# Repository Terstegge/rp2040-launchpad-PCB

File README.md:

# RP2040-Launchpad PCB

This repository contains the KiCad design files for a TI-style Launchpad board
with the RP2040 microcontroller. The board features a build-in picoprobe
debugger, which signals UART RX/TX and SWD activity with 3 LEDs. The unused
GPIO pins of the picoprobe are connected to a header, which could be used
in the future for more functionality like a simple logic analyzer etc.

The target RP2040 controller has 2 connected pushbuttons, one normal LED and
8 WS2812-2020 LEDs as input/output. Some signals are also available on a
horizonal header at the lower end of the PCB, which is used to connect WLAN or
Bluetooth boards like WifiTick. Both RP2040 (target and picoprobe) use a
4 MiB flash chip. The target RP2040 also has a button to enable programming
via the target USB port (mass storage device). Normally this button is
not needed, because all programming and debugging of the target is performed
via the picoprobe using openocd and gdb.

The board also contains a LiPo-charger to enable battery-powered projects.

Why was this board designed? I have been using the MSP432 Launchpad from TI for
quite a while in university classes teaching microcontroller technology.
Unfortunately TI has stopped producing all MSP432-related products. Still we
have purchased lots of TI boosterpack-boards like the Educational Boosterpack MK II.
The be able to used these Boosterpacks also in the future, a new Launchpad had
to be found. The RP2040 is a very interesting microcontroller, and, what is
quite important for educational purposes, it has excellent documentation.
So some days were spent and this board came to life.

The pictures below show version 1.1, which only had 2 WS2812 LEDS, which were
quite big and bright. The current version 1.2 contains 8 smaller WS2812-2020
LEDs. The pictures will be updated as soon as prototypes for the new version
are available.

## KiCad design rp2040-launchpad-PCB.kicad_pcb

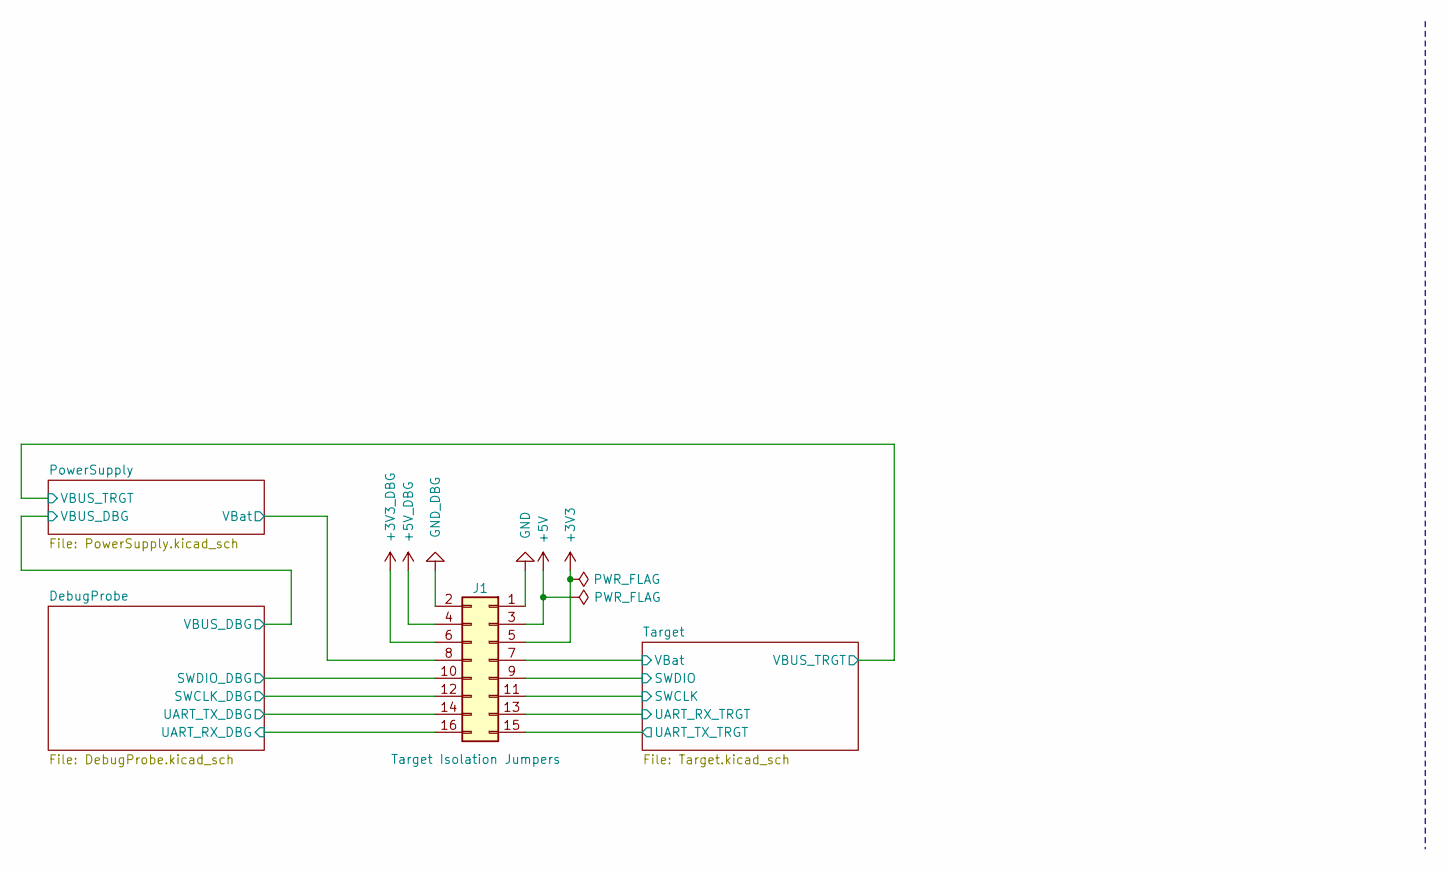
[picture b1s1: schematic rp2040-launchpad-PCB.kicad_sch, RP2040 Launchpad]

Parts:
J1: Target Isolation Jumpers; PinHeader_2x08_P2.54mm_Vertical

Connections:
+3V3: J1.5; also elsewhere on the board
+3V3_DBG: J1.6; also elsewhere on the board
+5V: J1.3; also elsewhere on the board
+5V_DBG: J1.4; also elsewhere on the board
/DebugProbe/SWCLK_DBG: J1.12; also elsewhere on the board
/DebugProbe/SWDIO_DBG: J1.10; also elsewhere on the board
/DebugProbe/UART_RX_DBG: J1.16; also elsewhere on the board
/DebugProbe/UART_TX_DBG: J1.14; also elsewhere on the board
/PowerSupply/VBat: J1.8; also elsewhere on the board
/Target/SWCLK: J1.11; also elsewhere on the board
/Target/SWDIO: J1.9; also elsewhere on the board
/Target/UART_RX_TRGT: J1.13; also elsewhere on the board
/Target/UART_TX_TRGT: J1.15; also elsewhere on the board
/Target/VBat: J1.7; also elsewhere on the board
GND: J1.1; also elsewhere on the board
GND_DBG: J1.2; also elsewhere on the board

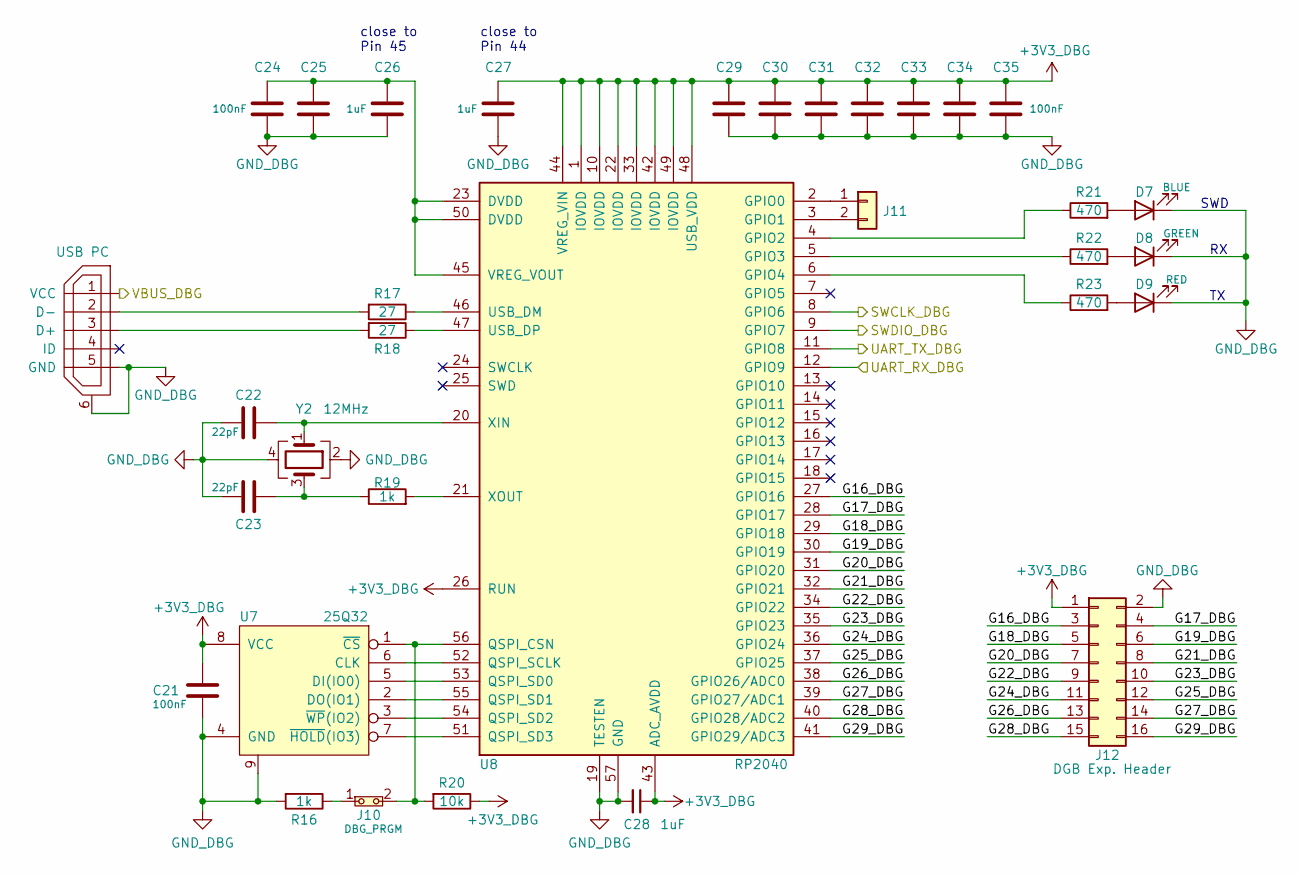
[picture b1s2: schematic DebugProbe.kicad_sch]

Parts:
C21, C24, C25, C29, C30, C31, C32, C33, C34, C35: 100nF; C_0603_1608Metric
C22, C23: 22pF; C_0603_1608Metric
C26, C27, C28: 1uF; C_0603_1608Metric
D7: BLUE; LED_0603_1608Metric
D8: GREEN; LED_0603_1608Metric
D9: RED; LED_0603_1608Metric
J10: DBG_PRGM; PinHeader_1x02_P2.54mm_Vertical
J11: UART_DBG; PinHeader_1x02_P2.54mm_Vertical
J12: DGB Exp. Header; PinHeader_2x08_P2.54mm_Vertical
R16, R19: 1k; R_0603_1608Metric
R17, R18: 27; R_0603_1608Metric
R20: 10k; R_0603_1608Metric
R21, R22, R23: 470; R_0603_1608Metric
U7: 25Q32; WSON-8-1EP_6x5mm_P1.27mm_EP3.4x4.3mm
U8: RP2040; QFN40P700X700X90-57N; PARTREV 1.6.1
USB2: USB PC; USB-micro-B-Amph-10118194
Y2: 12MHz; Crystal_SMD_TXC_7M-4Pin_3.2x2.5mm

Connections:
+3V3_DBG: C21.1, C27.1, C28.1, C29.1, C30.1, C31.1, C32.1, C33.1, C34.1, C35.1, J12.1, R20.1, U7.8 (VCC), U8.1 (IOVDD), U8.10 (IOVDD), U8.22 (IOVDD), U8.26 (RUN), U8.33 (IOVDD), U8.42 (IOVDD), U8.43 (ADC_AVDD), U8.44 (VREG_VIN), U8.48 (USB_VDD), U8.49 (IOVDD); also elsewhere on the board
/DebugProbe/G16_DBG: J12.3, U8.27 (GPIO16)
/DebugProbe/G17_DBG: J12.4, U8.28 (GPIO17)
/DebugProbe/G18_DBG: J12.5, U8.29 (GPIO18)
/DebugProbe/G19_DBG: J12.6, U8.30 (GPIO19)
/DebugProbe/G20_DBG: J12.7, U8.31 (GPIO20)
/DebugProbe/G21_DBG: J12.8, U8.32 (GPIO21)
/DebugProbe/G22_DBG: J12.9, U8.34 (GPIO22)
/DebugProbe/G23_DBG: J12.10, U8.35 (GPIO23)
/DebugProbe/G24_DBG: J12.11, U8.36 (GPIO24)
/DebugProbe/G25_DBG: J12.12, U8.37 (GPIO25)
/DebugProbe/G26_DBG: J12.13, U8.38 (GPIO26/ADC0)
/DebugProbe/G27_DBG: J12.14, U8.39 (GPIO27/ADC1)
/DebugProbe/G28_DBG: J12.15, U8.40 (GPIO28/ADC2)
/DebugProbe/G29_DBG: J12.16, U8.41 (GPIO29/ADC3)
/DebugProbe/SWCLK_DBG: U8.8 (GPIO6); also elsewhere on the board
/DebugProbe/SWDIO_DBG: U8.9 (GPIO7); also elsewhere on the board
/DebugProbe/UART_RX_DBG: U8.12 (GPIO9); also elsewhere on the board
/DebugProbe/UART_TX_DBG: U8.11 (GPIO8); also elsewhere on the board
/DebugProbe/VBUS_DBG: USB2.1 (VCC); also elsewhere on the board
GND_DBG: C21.2, C22.1, C23.1, C24.2, C25.2, C26.2, C27.2, C28.2, C29.2, C30.2, C31.2, C32.2, C33.2, C34.2, C35.2, D7.1 (K), D8.1 (K), D9.1 (K), J12.2, R16.2, U7.4 (GND), U7.9, U8.19 (TESTEN), U8.57 (GND), USB2.5 (GND), USB2.6, Y2.2, Y2.4; also elsewhere on the board
unnamed: C22.2, U8.20 (XIN), Y2.1
unnamed: C23.2, R19.1, Y2.3
unnamed: C24.1, C25.1, C26.1, U8.23 (DVDD), U8.45 (VREG_VOUT), U8.50 (DVDD)
unnamed: D7.2 (A), R21.2
unnamed: D8.2 (A), R22.2
unnamed: D9.2 (A), R23.2
unnamed: J10.1, R16.1
unnamed: J10.2, R20.2, U7.1 (~CS), U8.56 (QSPI_CSN)
unnamed: J11.1, U8.2 (GPIO0)
unnamed: J11.2, U8.3 (GPIO1)
unnamed: R17.1, U8.46 (USB_DM)
unnamed: R17.2, USB2.2 (D-)
unnamed: R18.1, U8.47 (USB_DP)
unnamed: R18.2, USB2.3 (D+)
unnamed: R19.2, U8.21 (XOUT)
unnamed: R21.1, U8.4 (GPIO2)
unnamed: R22.1, U8.5 (GPIO3)
unnamed: R23.1, U8.6 (GPIO4)
unnamed: U7.2 (DO(IO1)), U8.55 (QSPI_SD1)
unnamed: U7.3 (~WP(IO2)), U8.54 (QSPI_SD2)
unnamed: U7.5 (DI(IO0)), U8.53 (QSPI_SD0)
unnamed: U7.6 (CLK), U8.52 (QSPI_SCLK)
unnamed: U7.7 (~HOLD(IO3)), U8.51 (QSPI_SD3)

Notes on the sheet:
SWD
close to Pin 45
close to Pin 44

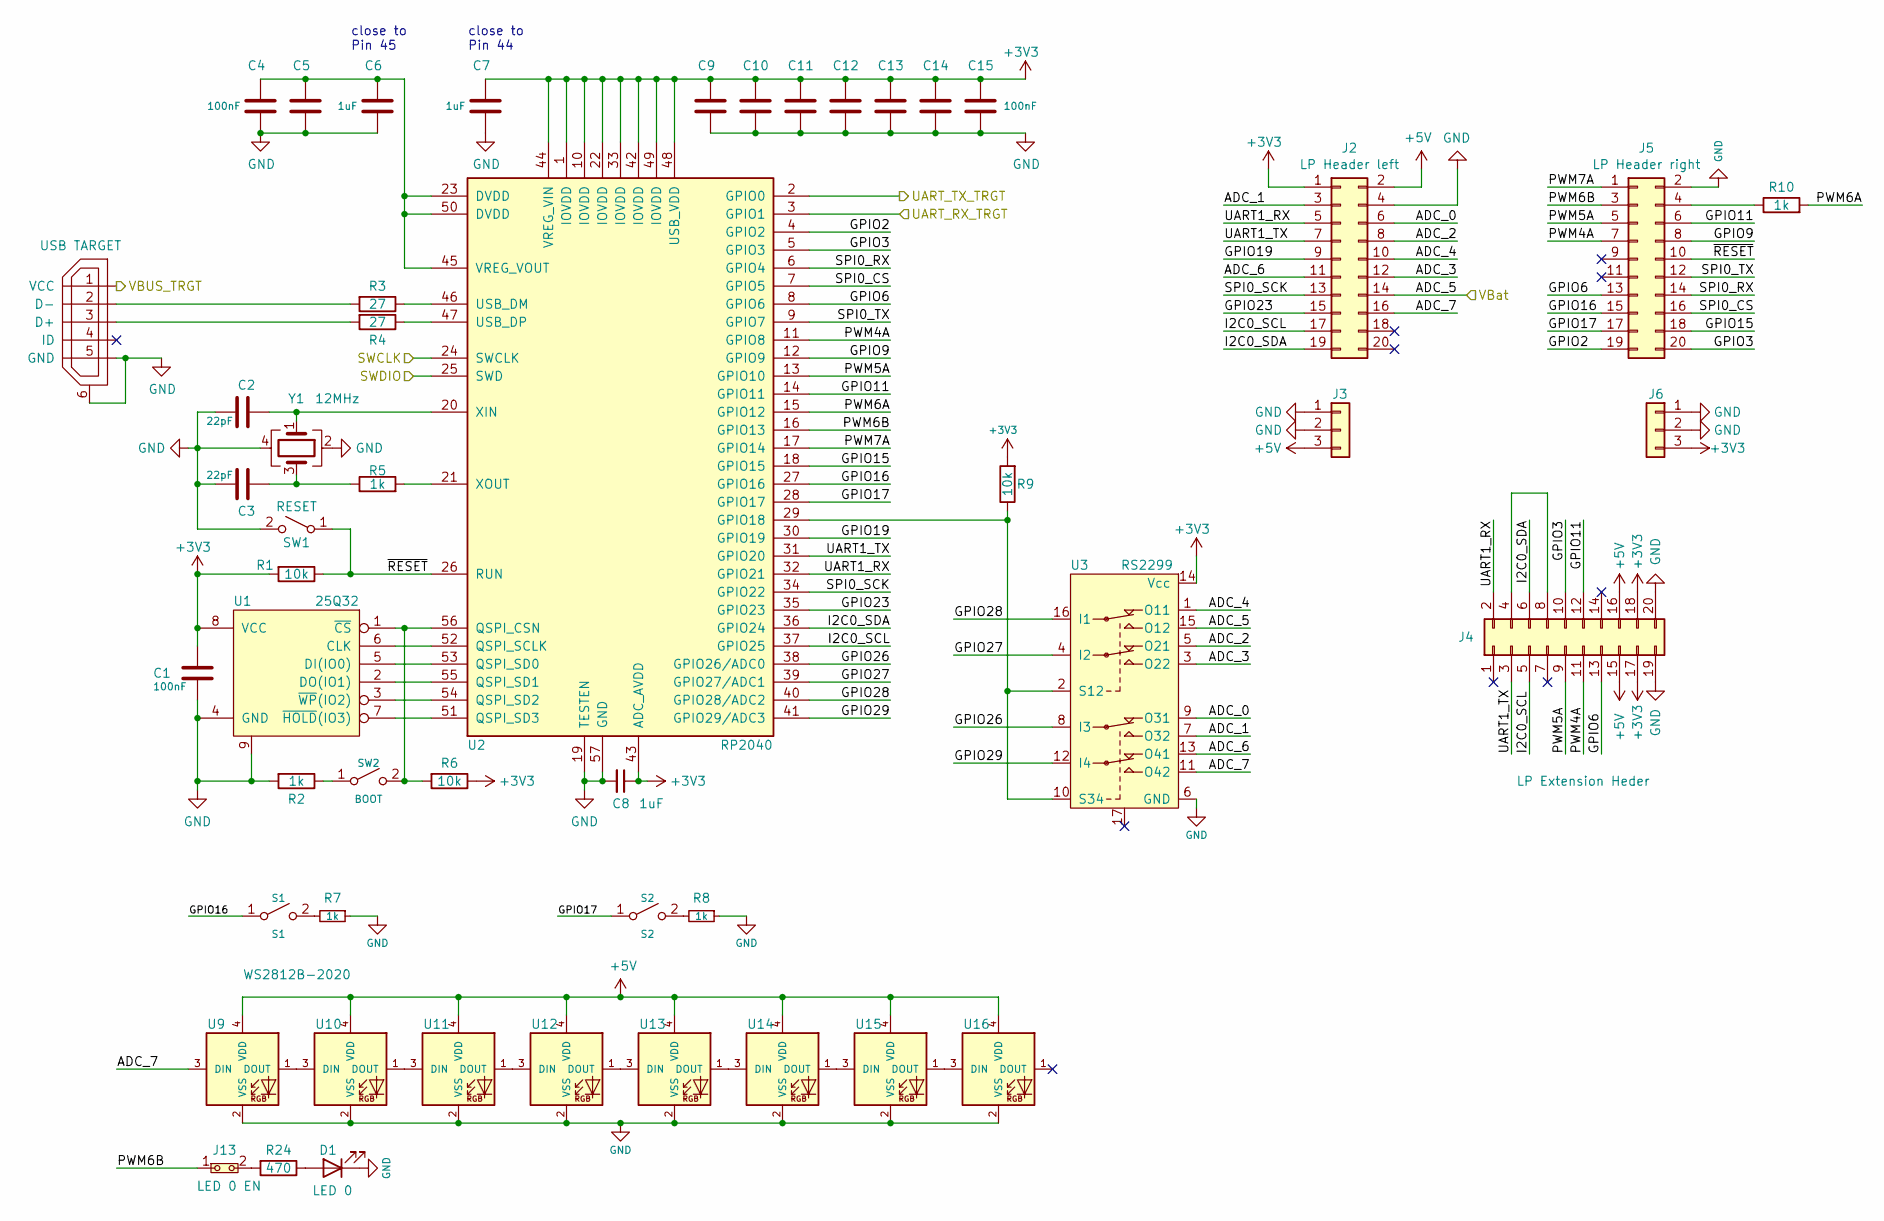
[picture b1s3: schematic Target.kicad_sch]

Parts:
C1, C4, C5, C9, C10, C11, C12, C13, C14, C15: 100nF; C_0603_1608Metric
C2, C3: 22pF; C_0603_1608Metric
C6, C7, C8: 1uF; C_0603_1608Metric
D1: LED 0; LED_0603_1608Metric
J2: LP Header left; PinHeader_2x10_P2.54mm_Vertical
J3, J6: PWR Header; PinHeader_1x03_P2.54mm_Vertical
J4: LP Extension Heder; PinHeader_2x10_P2.54mm_Vertical
J5: LP Header right; PinHeader_2x10_P2.54mm_Vertical
J13: LED 0 EN; PinHeader_1x02_P2.54mm_Vertical
R1, R6, R9: 10k; R_0603_1608Metric
R2, R5, R7, R8, R10: 1k; R_0603_1608Metric
R3, R4: 27; R_0603_1608Metric
R24: 470; R_0603_1608Metric
S1: S1; DIPT-1188E
S2: S2; DIPT-1188E
SW1: RESET; DIPT-1188E
SW2: BOOT; KMR2-Switch
U1: 25Q32; WSON-8-1EP_6x5mm_P1.27mm_EP3.4x4.3mm
U2: RP2040; QFN40P700X700X90-57N; PARTREV 1.6.1
U3: RS2299; QFN-16-1EP_3x3mm_P0.5mm_EP1.7x1.7mm
U9, U10, U11, U12, U13, U14, U15, U16: WS2812B-2020
USB1: USB TARGET; USB-micro-B-Amph-10118194
Y1: 12MHz; Crystal_SMD_TXC_7M-4Pin_3.2x2.5mm

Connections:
+3V3: C1.1, C7.1, C8.1, C9.1, C10.1, C11.1, C12.1, C13.1, C14.1, C15.1, J2.1, J4.17, J4.18, J6.3, R1.2, R6.1, R9.2, U1.8 (VCC), U2.1 (IOVDD), U2.10 (IOVDD), U2.22 (IOVDD), U2.33 (IOVDD), U2.42 (IOVDD), U2.43 (ADC_AVDD), U2.44 (VREG_VIN), U2.48 (USB_VDD), U2.49 (IOVDD), U3.14 (Vcc); also elsewhere on the board
+5V: J2.2, J3.3, J4.15, J4.16, U9.4 (VDD), U10.4 (VDD), U11.4 (VDD), U12.4 (VDD), U13.4 (VDD), U14.4 (VDD), U15.4 (VDD), U16.4 (VDD); also elsewhere on the board
/PowerSupply/VBUS_TRGT: USB1.1 (VCC); also elsewhere on the board
/Target/ADC_0: J2.6, U3.9 (O31)
/Target/ADC_1: J2.3, U3.7 (O32)
/Target/ADC_2: J2.8, U3.5 (O21)
/Target/ADC_3: J2.12, U3.3 (O22)
/Target/ADC_4: J2.10, U3.1 (O11)
/Target/ADC_6: J2.11, U3.13 (O41)
/Target/ADC_7: J2.16, U3.11 (O42), U9.3 (DIN)
/Target/GPIO2: J5.19, U2.4 (GPIO2)
/Target/GPIO3: J4.10, J5.20, U2.5 (GPIO3)
/Target/GPIO6: J4.13, J5.13, U2.8 (GPIO6)
/Target/GPIO9: J5.8, U2.12 (GPIO9)
/Target/GPIO11: J4.12, J5.6, U2.14 (GPIO11)
/Target/GPIO15: J5.18, U2.18 (GPIO15)
/Target/GPIO16: J5.15, S1.1 (A), U2.27 (GPIO16)
/Target/GPIO17: J5.17, S2.1 (A), U2.28 (GPIO17)
/Target/GPIO19: J2.9, U2.30 (GPIO19)
/Target/GPIO23: J2.15, U2.35 (GPIO23)
/Target/GPIO26: U2.38 (GPIO26/ADC0), U3.8 (I3)
/Target/GPIO27: U2.39 (GPIO27/ADC1), U3.4 (I2)
/Target/GPIO28: U2.40 (GPIO28/ADC2), U3.16 (I1)
/Target/GPIO29: U2.41 (GPIO29/ADC3), U3.12 (I4)
/Target/I2C0_SCL: J2.17, J4.5, U2.37 (GPIO25)
/Target/I2C0_SDA: J2.19, J4.6, U2.36 (GPIO24)
/Target/PWM4A: J4.11, J5.7, U2.11 (GPIO8)
/Target/PWM5A: J4.9, J5.5, U2.13 (GPIO10)
/Target/PWM6A: R10.2, U2.15 (GPIO12)
/Target/PWM6B: J5.3, J13.1, U2.16 (GPIO13)
/Target/PWM7A: J5.1, U2.17 (GPIO14)
/Target/SPI0_CS: J5.16, U2.7 (GPIO5)
/Target/SPI0_RX: J5.14, U2.6 (GPIO4)
/Target/SPI0_SCK: J2.13, U2.34 (GPIO22)
/Target/SPI0_TX: J5.12, U2.9 (GPIO7)
/Target/SWCLK: U2.24 (SWCLK); also elsewhere on the board
/Target/SWDIO: U2.25 (SWD); also elsewhere on the board
/Target/UART1_RX: J2.5, J4.2, U2.32 (GPIO21)
/Target/UART1_TX: J2.7, J4.3, U2.31 (GPIO20)
/Target/UART_RX_TRGT: U2.3 (GPIO1); also elsewhere on the board
/Target/UART_TX_TRGT: U2.2 (GPIO0); also elsewhere on the board
/Target/VBat: J2.14, U3.15 (O12); also elsewhere on the board
/Target/~RESET: J5.10, R1.1, SW1.1 (A), U2.26 (RUN)
GND: C1.2, C2.1, C3.1, C4.2, C5.2, C6.2, C7.2, C8.2, C9.2, C10.2, C11.2, C12.2, C13.2, C14.2, C15.2, D1.1 (K), J2.4, J3.1, J3.2, J4.19, J4.20, J5.2, J6.1, J6.2, R2.2, R7.1, R8.1, SW1.2 (B), U1.4 (GND), U1.9, U2.19 (TESTEN), U2.57 (GND), U3.6 (GND), U9.2 (VSS), U10.2 (VSS), U11.2 (VSS), U12.2 (VSS), U13.2 (VSS), U14.2 (VSS), U15.2 (VSS), U16.2 (VSS), USB1.5 (GND), USB1.6, Y1.2, Y1.4; also elsewhere on the board
unnamed: C2.2, U2.20 (XIN), Y1.1
unnamed: C3.2, R5.1, Y1.3
unnamed: C4.1, C5.1, C6.1, U2.23 (DVDD), U2.45 (VREG_VOUT), U2.50 (DVDD)
unnamed: D1.2 (A), R24.1
unnamed: J4.4, J4.8
unnamed: J5.4, R10.1
unnamed: J13.2, R24.2
unnamed: R2.1, SW2.1 (A)
unnamed: R3.1, U2.46 (USB_DM)
unnamed: R3.2, USB1.2 (D-)
unnamed: R4.1, U2.47 (USB_DP)
unnamed: R4.2, USB1.3 (D+)
unnamed: R5.2, U2.21 (XOUT)
unnamed: R6.2, SW2.2 (B), U1.1 (~CS), U2.56 (QSPI_CSN)
unnamed: R7.2, S1.2 (B)
unnamed: R8.2, S2.2 (B)
unnamed: R9.1, U2.29 (GPIO18), U3.2 (S12), U3.10 (S34)
unnamed: U1.2 (DO(IO1)), U2.55 (QSPI_SD1)
unnamed: U1.3 (~WP(IO2)), U2.54 (QSPI_SD2)
unnamed: U1.5 (DI(IO0)), U2.53 (QSPI_SD0)
unnamed: U1.6 (CLK), U2.52 (QSPI_SCLK)
unnamed: U1.7 (~HOLD(IO3)), U2.51 (QSPI_SD3)
unnamed: U10.1 (DOUT), U11.3 (DIN)
unnamed: U9.1 (DOUT), U10.3 (DIN)
unnamed: U11.1 (DOUT), U12.3 (DIN)
unnamed: U12.1 (DOUT), U13.3 (DIN)
unnamed: U13.1 (DOUT), U14.3 (DIN)
unnamed: U14.1 (DOUT), U15.3 (DIN)
unnamed: U15.1 (DOUT), U16.3 (DIN)

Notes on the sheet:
close to Pin 44
close to Pin 45

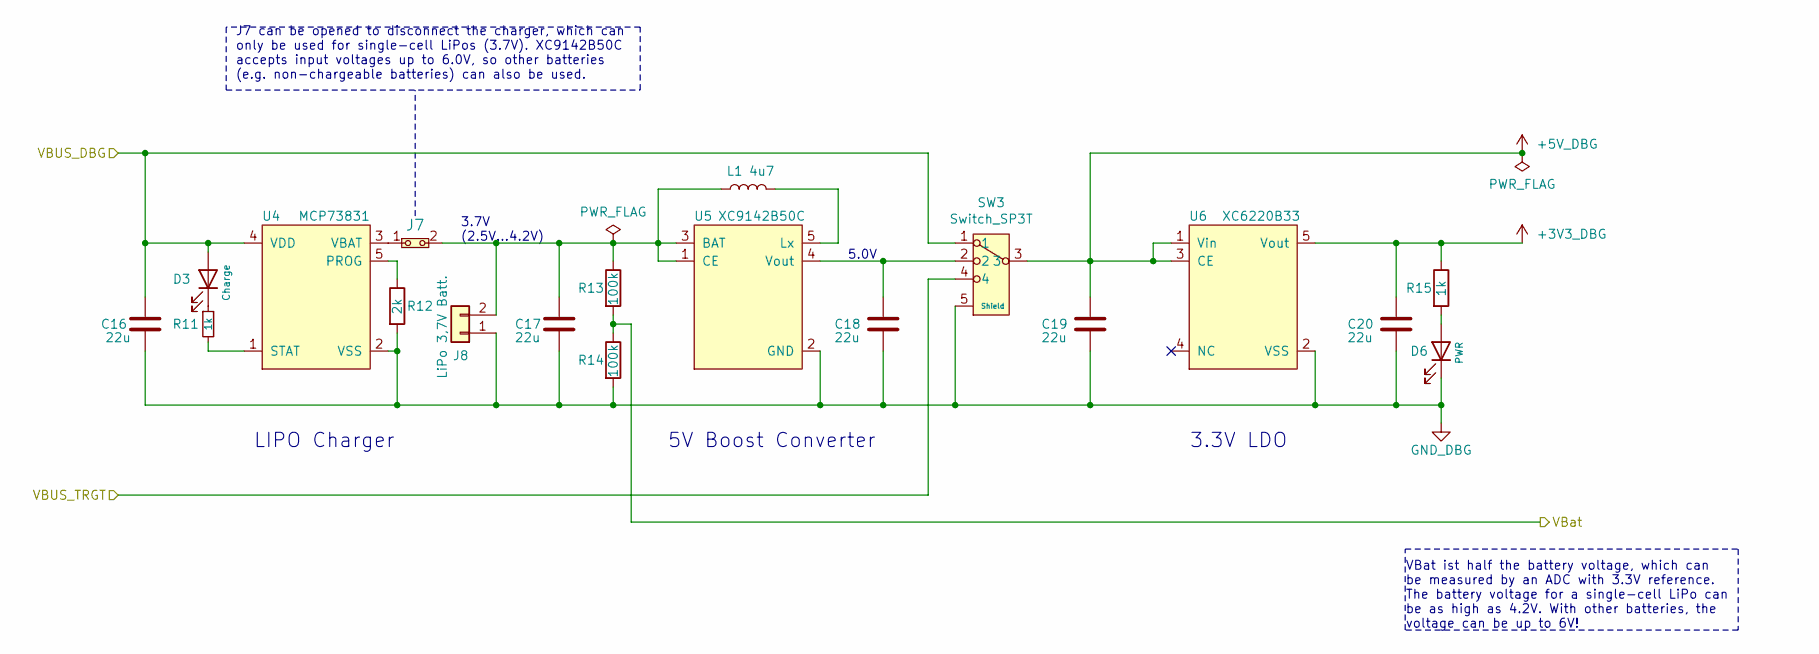
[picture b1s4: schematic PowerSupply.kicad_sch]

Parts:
C16, C17, C18, C19, C20: 22u; C_0805_2012Metric
D3: Charge; LED_0603_1608Metric
D6: PWR; LED_0603_1608Metric
J7: Jumper; SolderJumper-2_P1.3mm_Bridged_RoundedPad1.0x1.5mm
J8: LiPo 3,7V Batt.; JST-S2B-PH-KL
L1: 4u7; L_1008_2520Metric
R11, R15: 1k; R_0603_1608Metric
R12: 2k; R_0603_1608Metric
R13, R14: 100k; R_0603_1608Metric
SW3: Switch_SP3T; PCM13SMTR
U4: MCP73831; SOT-23-5
U5: XC9142B50C; SOT-23-5
U6: XC6220B33; SOT-23-5

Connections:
+3V3_DBG: C20.2, R15.1, U6.5 (Vout); also elsewhere on the board
+5V_DBG: C19.2, SW3.3, U6.1 (Vin), U6.3 (CE); also elsewhere on the board
/DebugProbe/VBUS_DBG: C16.2, D3.2 (A), SW3.1, U4.4 (VDD); also elsewhere on the board
/PowerSupply/VBUS_TRGT: SW3.4; also elsewhere on the board
/PowerSupply/VBat: R13.2, R14.1; also elsewhere on the board
GND_DBG: C16.1, C17.1, C18.1, C19.1, C20.1, D6.1 (K), J8.1, R12.2, R14.2, SW3.5 (Shield), U4.2 (VSS), U5.2 (GND), U6.2 (VSS); also elsewhere on the board
unnamed: C17.2, J7.2, J8.2, L1.1, R13.1, U5.1 (CE), U5.3 (BAT)
unnamed: C18.2, SW3.2, U5.4 (Vout)
unnamed: D3.1 (K), R11.1
unnamed: D6.2 (A), R15.2
unnamed: J7.1, U4.3 (VBAT)
unnamed: L1.2, U5.5 (Lx)
unnamed: R11.2, U4.1 (STAT)
unnamed: R12.1, U4.5 (PROG)

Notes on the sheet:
3.7V (2.5V...4.2V)
3.3V LDO
5V Boost Converter
VBat ist half the battery voltage, which can be measured by an ADC with 3.3V reference. The battery voltage for a single-cell LiPo can be as high as 4.2V. With other batteries, the voltage can be up to 6V!
LIPO Charger
J7 can be opened to disconnect the charger, which can only be used for single-cell LiPos (3.7V). XC9142B50C accepts input voltages up to 6.0V, so other batteries (e.g. non-chargeable batteries) can also be used.
5.0V

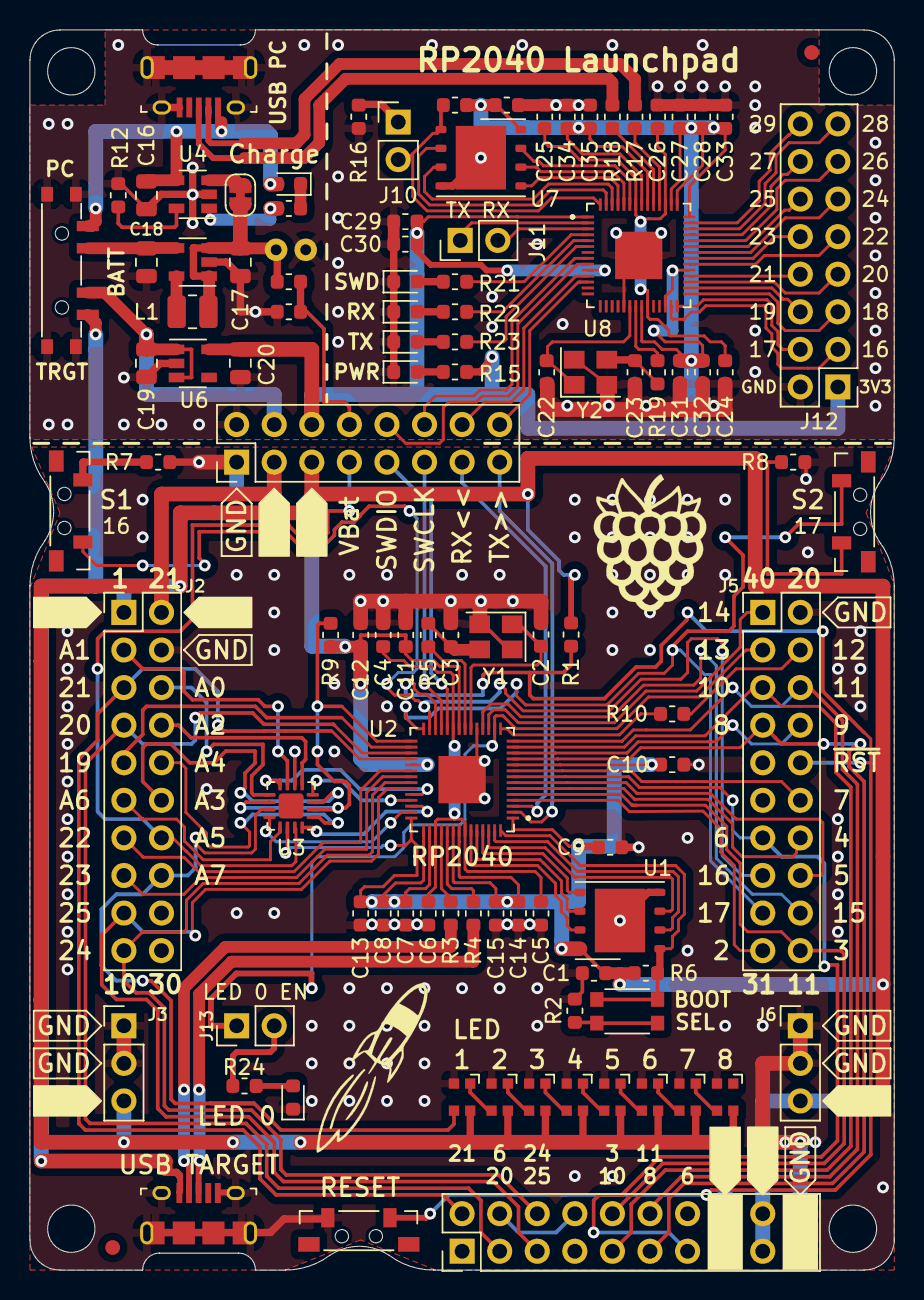
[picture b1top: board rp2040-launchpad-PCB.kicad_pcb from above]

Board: 2 copper layers, 58.4 x 83.8 mm, 103 parts (1 on the bottom side), 127 nets.

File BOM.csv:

ID;Bezeichner;Gehäuse;Stückzahl;Bezeichnung;Anbieter und Referenz
;;;;;
1;C1,C4,C5,C9,C10,C11,C12,C13,C14,C15,C21,C24,C25,C29,C30,C31,C32,C33,C34,C35;C_0603_1608Metric;20;100nF;
2;C16,C17,C18,C19,C20;C_0805_2012Metric;5;22u;
3;C2,C3,C22,C23;C_0603_1608Metric;4;22pF;
4;C6,C7,C8,C26,C27,C28;C_0603_1608Metric;6;1uF;
5;D1;LED_0603_1608Metric;1;LED 0;
6;D3;LED_0603_1608Metric;1;Charge;
7;D6;LED_0603_1608Metric;1;PWR;
8;D7;LED_0603_1608Metric;1;BLUE;
9;D8;LED_0603_1608Metric;1;GREEN;
10;D9;LED_0603_1608Metric;1;RED;
11;G***;Lauchpad-Logo;1;LOGO;
12;G***,G***;raspberry;2;LOGO;
13;G***,G***;Lauchpad-Energia-Logo;2;LOGO;
14;J1;PinHeader_2x08_P2.54mm_Vertical;1;Target Isolation Jumpers;
15;J10;PinHeader_1x02_P2.54mm_Vertical;1;DBG_PRGM;
16;J11;PinHeader_1x02_P2.54mm_Vertical;1;UART_DBG;
17;J12;PinHeader_2x08_P2.54mm_Vertical;1;DGB Exp. Header;
18;J13;PinHeader_1x02_P2.54mm_Vertical;1;LED 0 EN;
19;J2;PinHeader_2x10_P2.54mm_Vertical;1;LP Header left;
20;J3,J6;PinHeader_1x03_P2.54mm_Vertical;2;PWR Header;
21;J4;PinHeader_2x10_P2.54mm_Vertical;1;LP Extension Heder;
22;J5;PinHeader_2x10_P2.54mm_Vertical;1;LP Header right;
23;J7;SolderJumper-2_P1.3mm_Bridged_RoundedPad1.0x1.5mm;1;Jumper;
24;J8;JST-S2B-PH-KL;1;LiPo 3,7V Batt.;
25;L1;L_1008_2520Metric;1;4u7;
26;R1,R6,R9,R20;R_0603_1608Metric;4;10k;
27;R11,R2,R5,R7,R8,R10,R15,R16,R19;R_0603_1608Metric;9;1k;
28;R12;R_0603_1608Metric;1;2k;
29;R13,R14;R_0603_1608Metric;2;100k;
30;R21,R22,R23,R24;R_0603_1608Metric;4;470;
31;R3,R4,R17,R18;R_0603_1608Metric;4;27;
32;REF**,REF**;Fiducial_1mm_Mask2mm;2;Fiducial_1mm_Mask2mm;
33;S1;DIPT-1188E;1;S1;
34;S2;DIPT-1188E;1;S2;
35;SW1;DIPT-1188E;1;RESET;
36;SW2;KMR2-Switch;1;BOOT;
37;SW3;PCM13SMTR;1;Switch_SP3T;
38;U1,U7;WSON-8-1EP_6x5mm_P1.27mm_EP3.4x4.3mm;2;25Q32;
39;U2,U8;QFN40P700X700X90-57N;2;RP2040;
40;U3;QFN-16-1EP_3x3mm_P0.5mm_EP1.7x1.7mm;1;RS2299;
41;U4;SOT-23-5;1;MCP73831;
42;U5;SOT-23-5;1;XC9142B50C;
43;U6;SOT-23-5;1;XC6220B33;
44;U9,U10,U11,U12,U13,U14,U15,U16;WS2812B-2020;8;WS2812B-2020;
45;USB1;USB-micro-B-Amph-10118194;1;USB TARGET;
46;USB2;USB-micro-B-Amph-10118194;1;USB PC;
47;Y1,Y2;Crystal_SMD_TXC_7M-4Pin_3.2x2.5mm;2;12MHz;

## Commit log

2022-10-27 First commit with local version.
2022-10-27 Added picture.
2022-10-27 Added picture in README.
2022-10-27 Update README.md
    Updated README
2022-10-27 Update README.md
    Corrected 2 typos in README
2022-10-27 Added schematic file. Added gerber files. Updated README.
2022-10-27 Update README.md
    Another typo...
2022-11-02 Changed Raspberry logo. Added more vias around LiPo charger.
2022-11-02 Small fix in layout below rp2040 (probe).
2022-11-02 Updated BOM and logo (png)
2022-11-22 Added Pin1 silk for WS2812-2020 footprint. Generated new pos-Files because U9-U16 were missing.
2023-01-27 New version 1.3 - first commit
2023-01-27 Deleted double footprint folder - regenerated all production files just to be sure...
2023-01-27 BOM updated
2023-03-08 Version v1.3 finalized. Ready for production!
2023-04-13 Smaller changes and BOM update.
2024-03-11 Added new picture of v1.3 version.
2024-03-11 Updated README with new picture.
2024-09-01 Migration to KiCad version 8

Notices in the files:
rp2040-launchpad-PCB.kicad_pcb:
© A. Terstegge
